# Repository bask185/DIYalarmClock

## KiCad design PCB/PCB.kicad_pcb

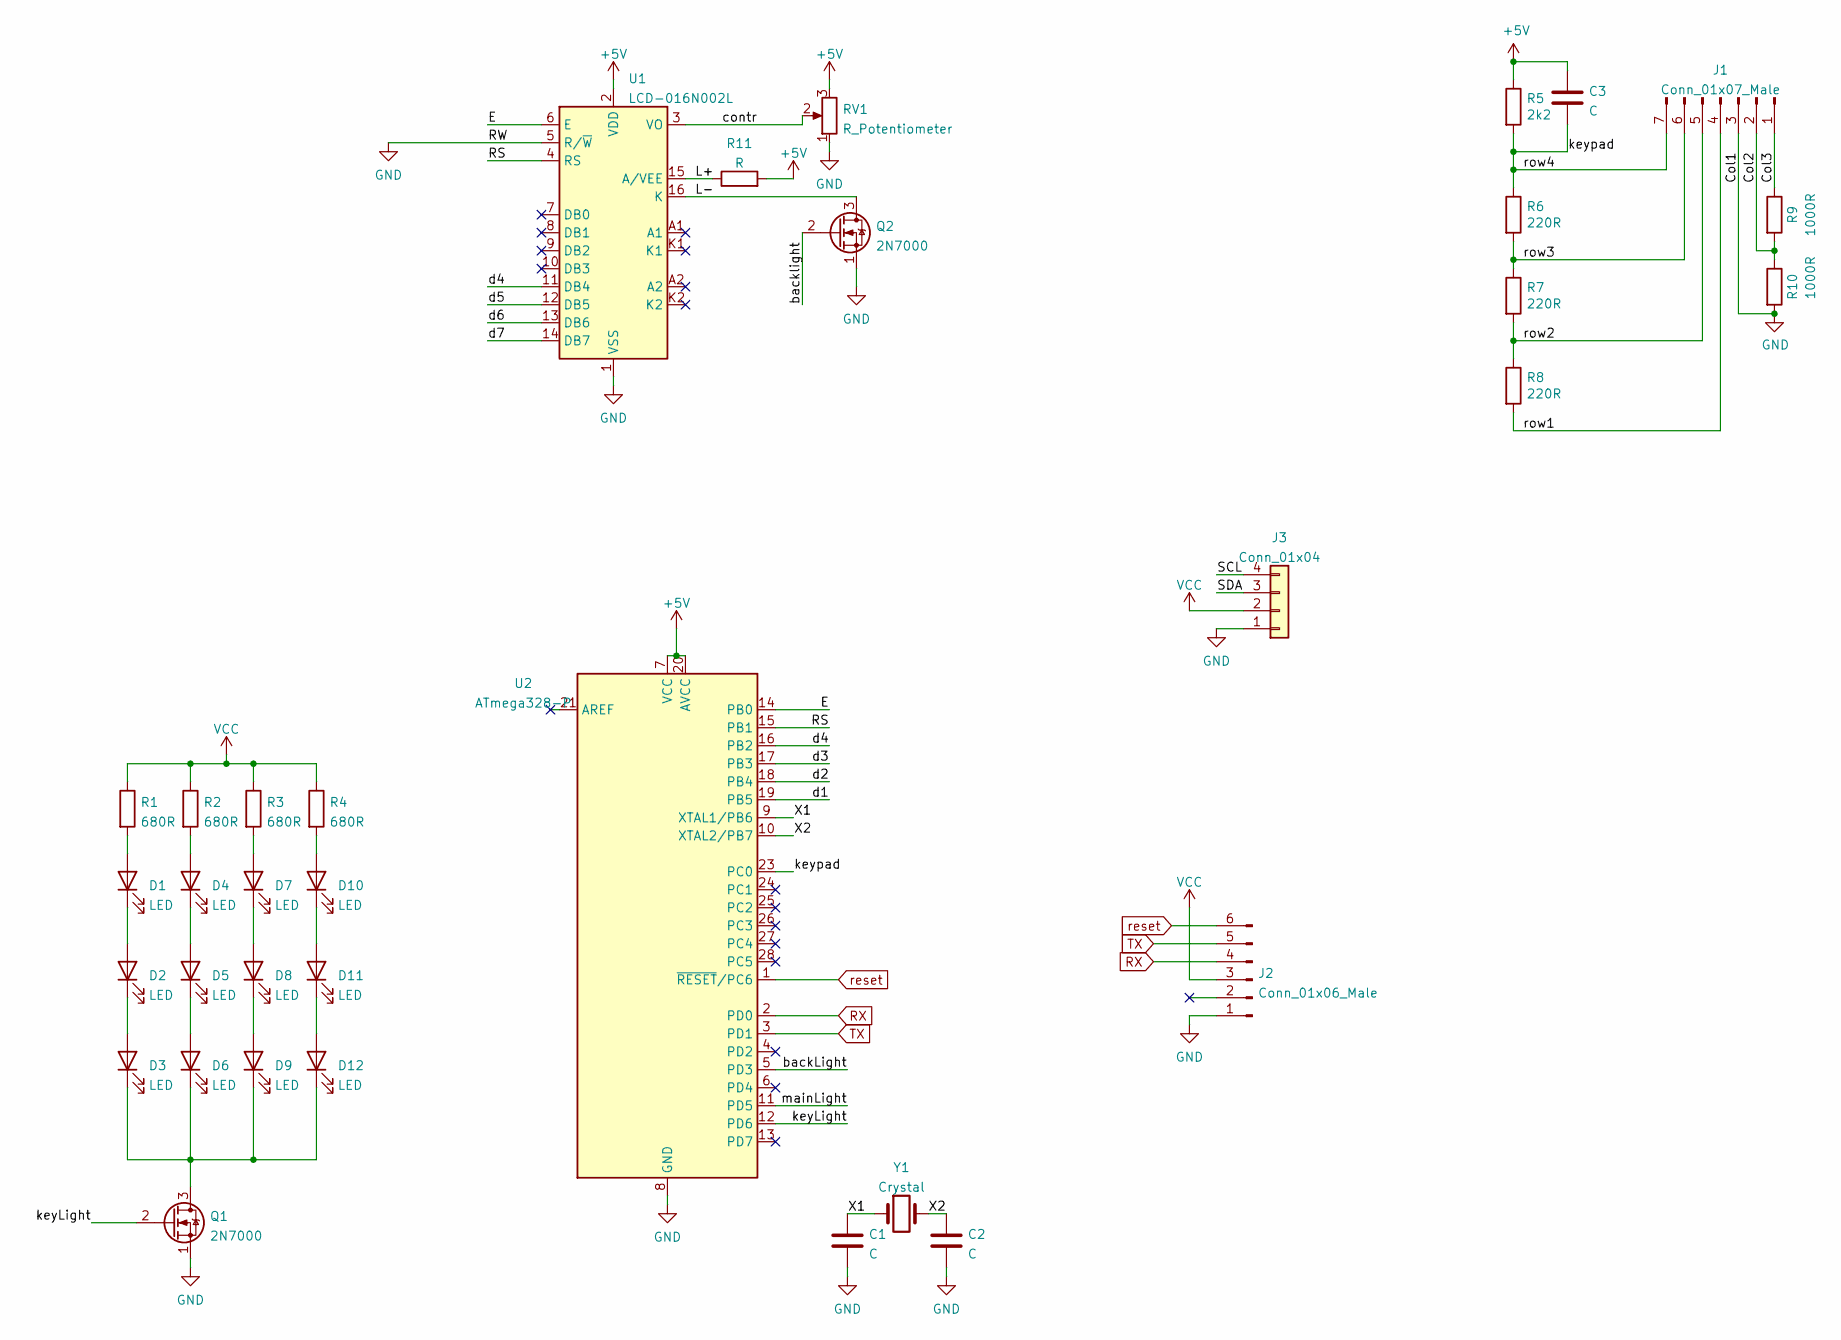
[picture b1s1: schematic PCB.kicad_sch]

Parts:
C1, C2, C3: C; C_Disc_D3.0mm_W1.6mm_P2.50mm
D1, D2, D3, D4, D5, D6, D7, D8, D9, D10, D11, D12: LED; LED_D3.0mm
J1: Conn_01x07_Male; PinHeader_1x07_P2.54mm_Vertical
J2: Conn_01x06_Male; PinHeader_1x06_P2.54mm_Vertical
J3: Conn_01x04; PinHeader_1x04_P2.54mm_Vertical
Q1, Q2: 2N7000; TO-92_Inline
R1, R2, R3, R4: 680R; R_Axial_DIN0204_L3.6mm_D1.6mm_P7.62mm_Horizontal
R5: 2k2; R_Axial_DIN0204_L3.6mm_D1.6mm_P7.62mm_Horizontal
R6, R7, R8: 220R; R_Axial_DIN0204_L3.6mm_D1.6mm_P7.62mm_Horizontal
R9, R10: 1000R; R_Axial_DIN0204_L3.6mm_D1.6mm_P7.62mm_Horizontal
R11: R; R_Axial_DIN0204_L3.6mm_D1.6mm_P7.62mm_Horizontal
RV1: R_Potentiometer; Potentiometer_Runtron_RM-065_Vertical
U1: LCD-016N002L; WC1602A
U2: ATmega328-P; DIP-28_W7.62mm
Y1: Crystal; Crystal_HC18-U_Vertical

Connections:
+5V: C3.1, R5.1, R11.2, RV1.3, U1.2 (VDD), U2.7 (VCC), U2.20 (AVCC)
/Col2: J1.2, R9.2, R10.1
/Col3: J1.1, R9.1
/E: U1.6 (E), U2.14 (PB0)
/L+: R11.1, U1.15 (A/VEE)
/L-: Q2.3 (D), U1.16 (K)
/RS: U1.4 (RS), U2.15 (PB1)
/SCL: J3.4
/SDA: J3.3
/X1: C1.1, U2.9 (XTAL1/PB6), Y1.1
/X2: C2.1, U2.10 (XTAL2/PB7), Y1.2
/backLight: U2.5 (PD3)
/backlight: Q2.2 (G)
/contr: RV1.2, U1.3 (VO)
/d1: U2.19 (PB5)
/d2: U2.18 (PB4)
/d3: U2.17 (PB3)
/d4: U1.11 (DB4), U2.16 (PB2)
/d5: U1.12 (DB5)
/d6: U1.13 (DB6)
/d7: U1.14 (DB7)
/keyLight: Q1.2 (G), U2.12 (PD6)
/keypad: C3.2, J1.7, R5.2, R6.1, U2.23 (PC0)
/mainLight: U2.11 (PD5)
/row1: J1.4, R8.2
/row2: J1.5, R7.2, R8.1
/row3: J1.6, R6.2, R7.1
GND: C1.2, C2.2, J1.3, J2.1, J3.1, Q1.1 (S), Q2.1 (S), R10.2, RV1.1, U1.1 (VSS), U1.5 (R/~W), U2.8 (GND), U2.22 (GND)
unnamed: D1.1 (K), D2.2 (A)
unnamed: D1.2 (A), R1.2
unnamed: D2.1 (K), D3.2 (A)
unnamed: D4.1 (K), D5.2 (A)
unnamed: D4.2 (A), R2.2
unnamed: D5.1 (K), D6.2 (A)
unnamed: D7.1 (K), D8.2 (A)
unnamed: D7.2 (A), R3.2
unnamed: D8.1 (K), D9.2 (A)
unnamed: D10.1 (K), D11.2 (A)
unnamed: D10.2 (A), R4.2
unnamed: D11.1 (K), D12.2 (A)
unnamed: D3.1 (K), D6.1 (K), D9.1 (K), D12.1 (K), Q1.3 (D)
RX: J2.4, U2.2 (PD0)
TX: J2.5, U2.3 (PD1)
VCC: J2.3, J3.2, R1.1, R2.1, R3.1, R4.1
reset: J2.6, U2.1 (~RESET/PC6)

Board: 2 copper layers, 35 parts (0 on the bottom side), 34 nets, no tracks yet.
